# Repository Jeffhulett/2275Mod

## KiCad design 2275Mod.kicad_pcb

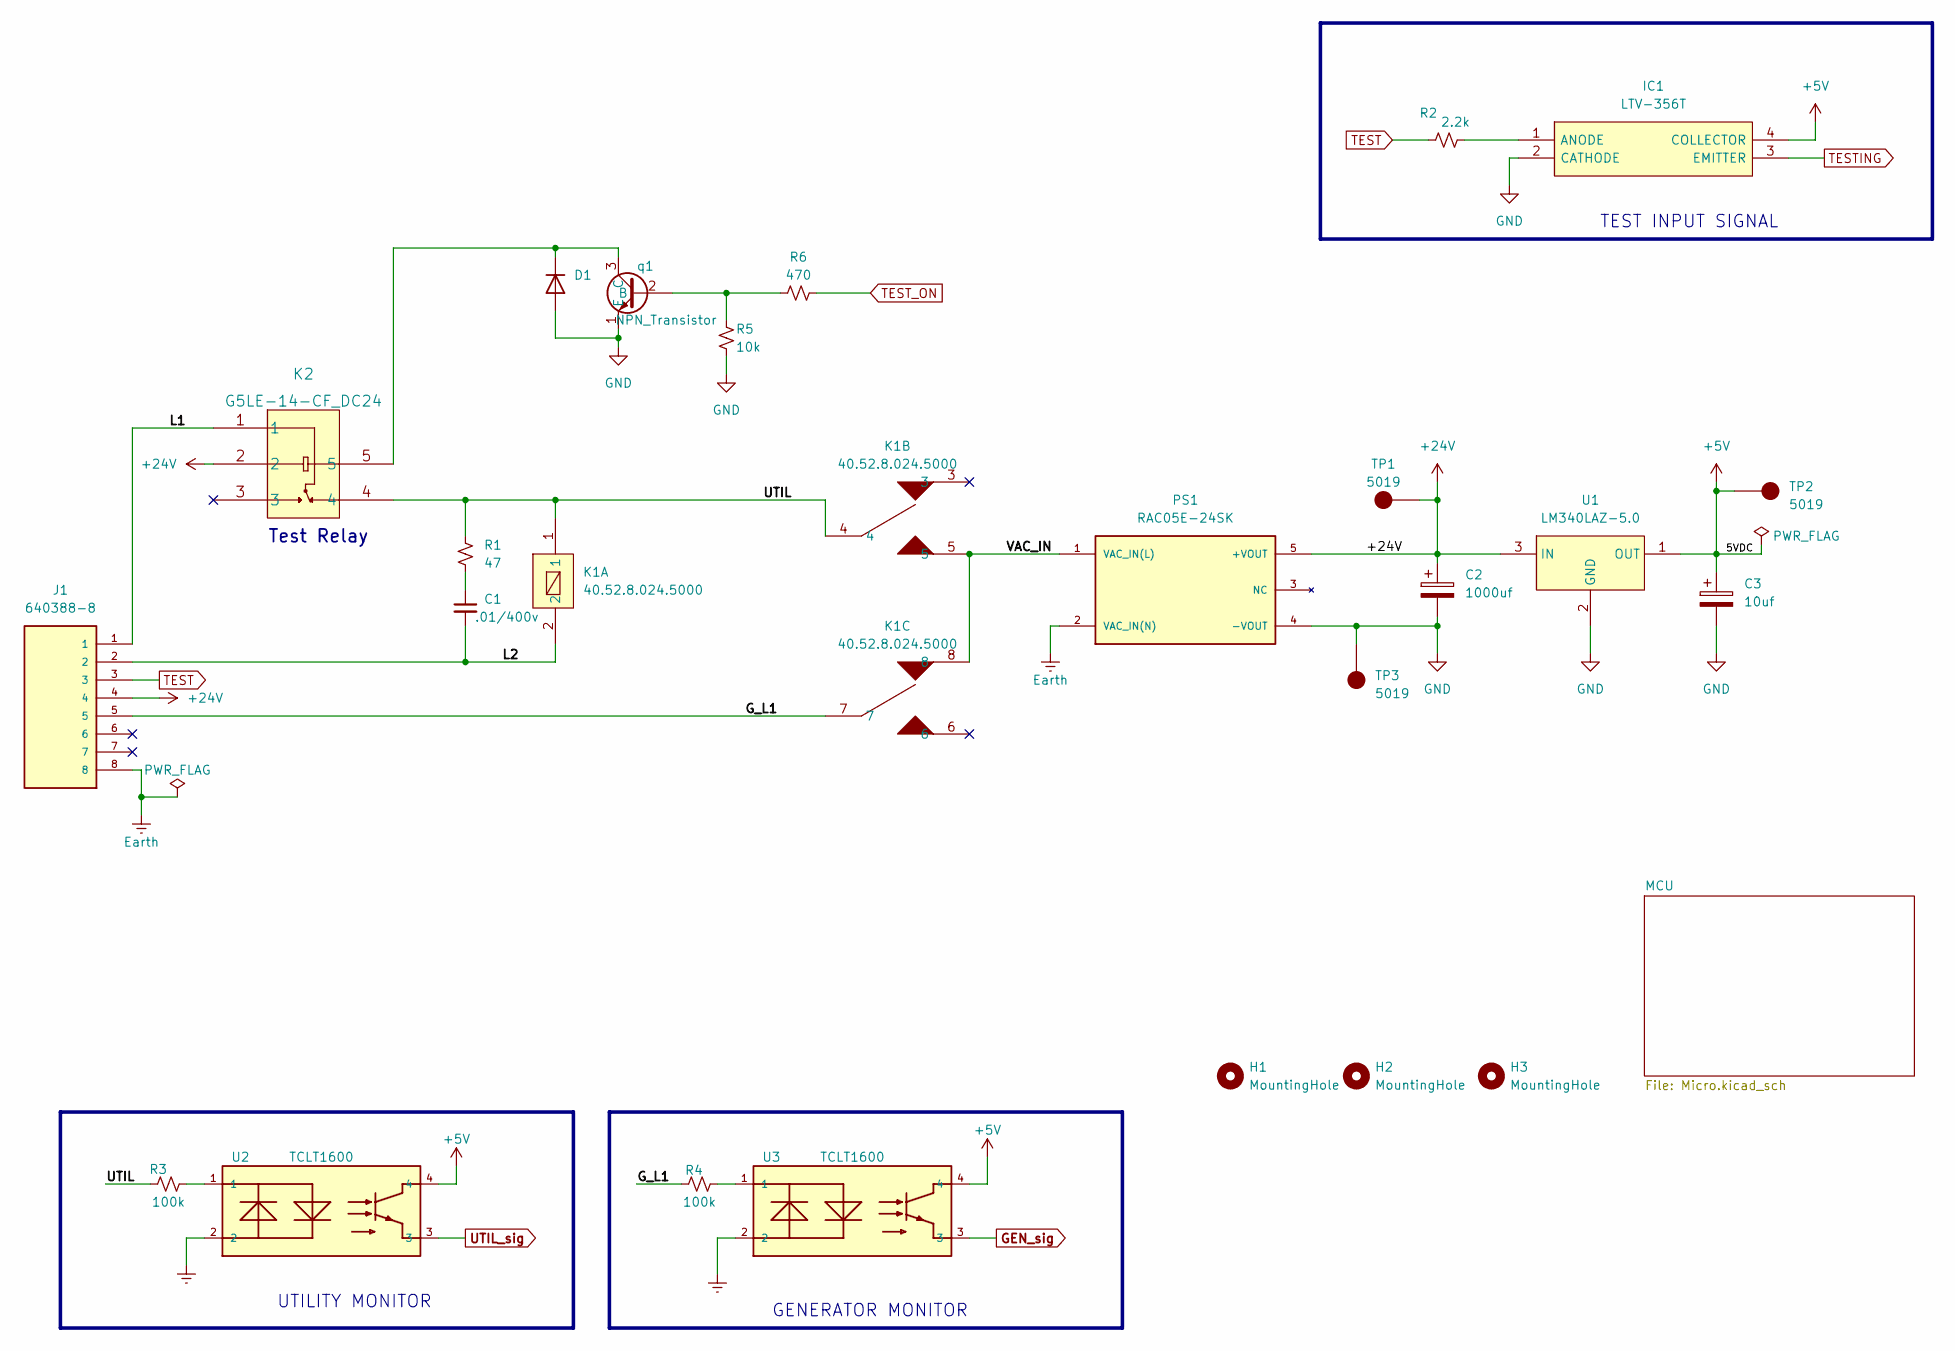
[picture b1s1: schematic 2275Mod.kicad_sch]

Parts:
C1: .01/400v; C_Rect_L9.0mm_W3.8mm_P7.50mm_MKT
C2: 1000uf; CP_Radial_D16.0mm_P7.50mm
C3: 10uf; CP_Radial_D5.0mm_P2.50mm
D1: MRA4007T3G; D_SMA
H1, H2, H3: MountingHole; MountingHole_3.7mm
IC1: LTV-356T; SOP254P675X220-4N; Mouser Part Number 859-LTV-356T
J1: 640388-8; TE_640388-8; Digi-Key part# A19906-ND
K1: 40.52.8.024.5000; 4052; Digi-Key 2066-40.52.8.024.5000-ND
K2: G5LE-14-CF_DC24; G5LE-14-CF DC24
PS1: RAC05E-24SK; CONV_RAC05E-24SK; PARTREV 0/2021
R1: 47; R_0805_2012Metric_Pad1.20x1.40mm_HandSolder
R2: 2.2k; R_0603_1608Metric_Pad0.98x0.95mm_HandSolder
R3, R4: 100k; R_1206_3216Metric_Pad1.30x1.75mm_HandSolder; Digi-Key 738-RNCP1206FTD100KCT-ND
R5: 10k; R_0603_1608Metric_Pad0.98x0.95mm_HandSolder
R6: 470; R_0603_1608Metric_Pad0.98x0.95mm_HandSolder
TP1, TP2, TP3: 5019; KEYSTONE_5019; PARTREV D
U1: LM340LAZ-5.0; TO92127P478H483-3; Digi-Key 2156-LM340LAZ-5.0-ND
U2, U3: TCLT1600; SOP254P1015X230-4N; Digi-Key TCLT1600CT-ND
q1: NPN_Transistor; SOT-23-3

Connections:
+5V: C3.1, IC1.4 (COLLECTOR), TP2.TP, U1.1 (OUT), U2.4, U3.4; also elsewhere on the board
+24V: C2.1, J1.4, K2.2, PS1.5 (+VOUT), TP1.TP, U1.3 (IN); also elsewhere on the board
/G_L1: J1.5, K1.7, R4.1
/L1: J1.1, K2.1
/L2: C1.2, J1.2, K1.2
/UTIL: K1.1, K1.4, K2.4, R1.1, R3.1
/VAC_IN: K1.5, K1.8, PS1.1 (VAC_IN(L))
Earth: J1.8, PS1.2 (VAC_IN(N)), U2.2, U3.2
GEN_sig: U3.3; also elsewhere on the board
GND: C2.2, C3.2, D1.2 (A), IC1.2 (CATHODE), PS1.4 (-VOUT), R5.2, TP3.TP, U1.2 (GND), q1.1 (E); also elsewhere on the board
unnamed: C1.1, R1.2
unnamed: D1.1 (K), K2.5, q1.3 (C)
unnamed: IC1.1 (ANODE), R2.2
unnamed: R3.2, U2.1
unnamed: R4.2, U3.1
unnamed: R5.1, R6.1, q1.2 (B)
TEST: J1.3, R2.1
TESTING: IC1.3 (EMITTER); also elsewhere on the board
TEST_ON: R6.2; also elsewhere on the board
UTIL_sig: U2.3; also elsewhere on the board

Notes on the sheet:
TEST INPUT SIGNAL
Test Relay
GENERATOR MONITOR
UTILITY MONITOR

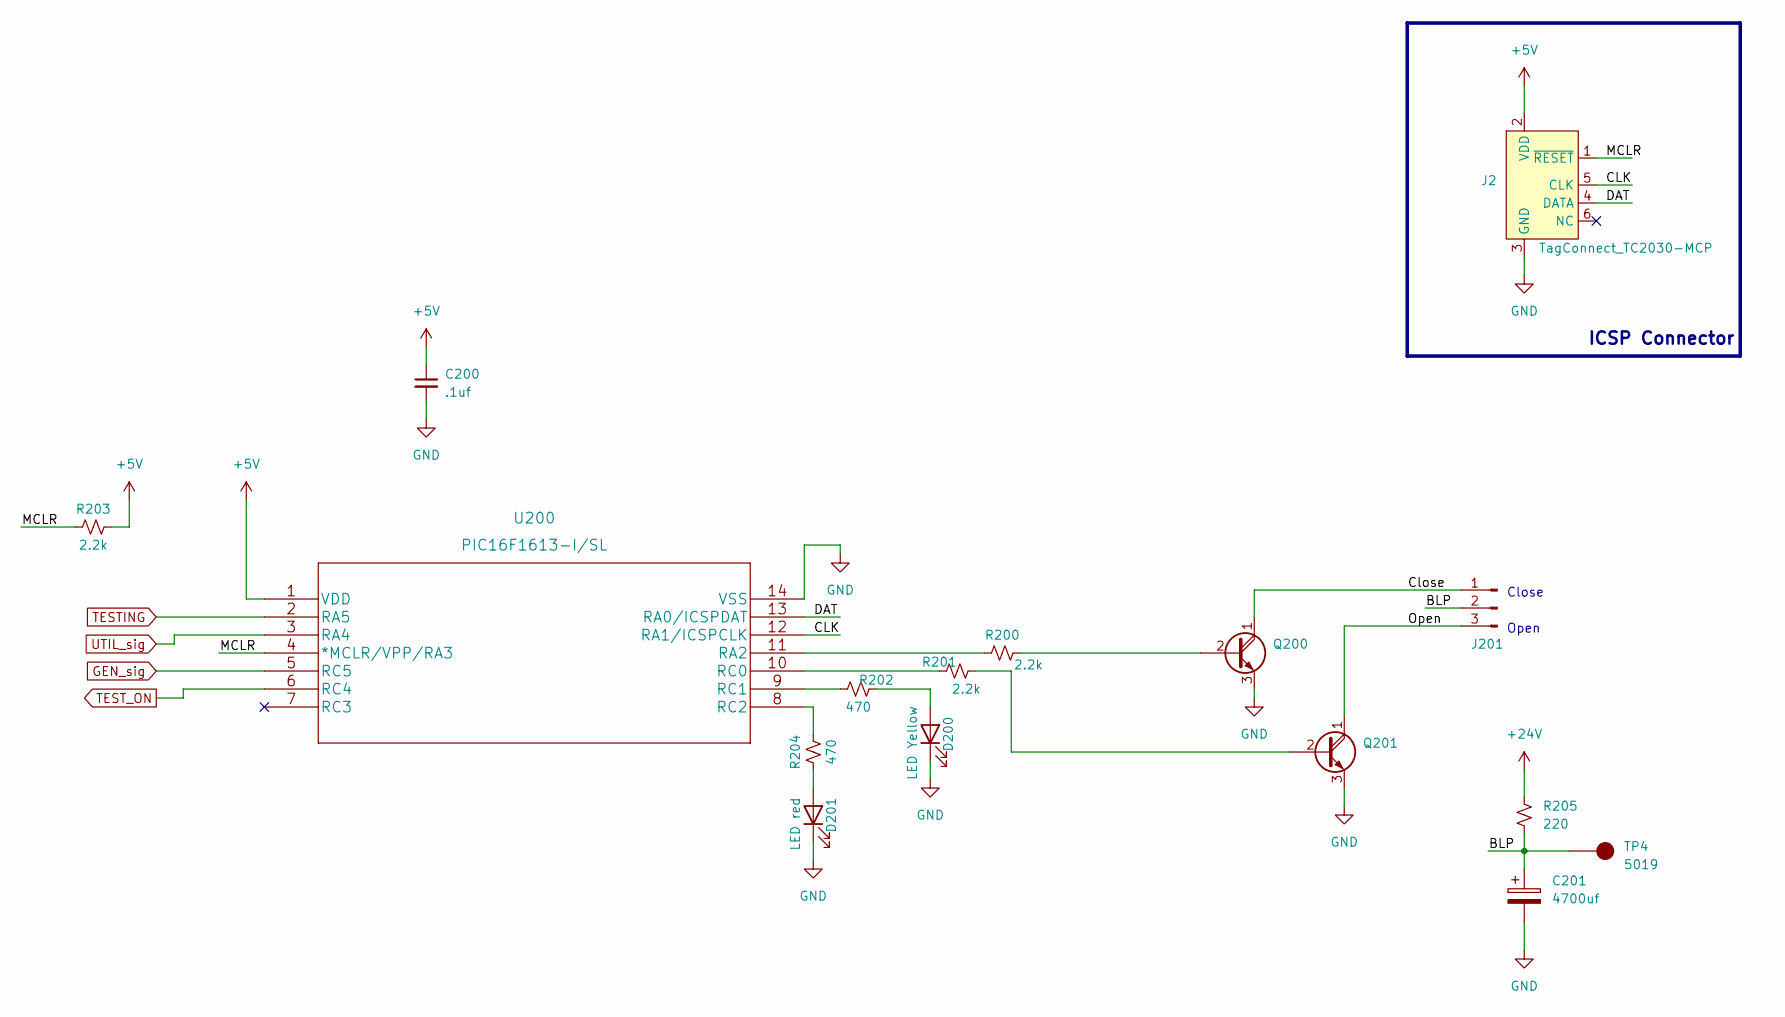
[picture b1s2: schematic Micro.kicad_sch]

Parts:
C200: .1uf; C_0603_1608Metric_Pad1.08x0.95mm_HandSolder
C201: 4700uf; CP_Radial_D25.0mm_P10.00mm_SnapIn
D200: LED Yellow; LED_0603_1608Metric_Pad1.05x0.95mm_HandSolder
D201: LED red; LED_0603_1608Metric_Pad1.05x0.95mm_HandSolder
J2: TagConnect_TC2030-MCP; Tag-Connect_TC2030-IDC-NL_2x03_P1.27mm_Vertical
J201: Conn_01x03_Male; PinHeader_1x03_P2.54mm_Vertical
Q200, Q201: Q_NPN_Darlington_CBE; SOT-223-3_TabPin2; Digi-Key FZT600BCT-ND
R200, R201, R203: 2.2k; R_0603_1608Metric_Pad0.98x0.95mm_HandSolder
R202, R204: 470; R_0805_2012Metric_Pad1.20x1.40mm_HandSolder
R205: 220; R_0805_2012Metric_Pad1.20x1.40mm_HandSolder
TP4: 5019; KEYSTONE_5019; PARTREV D
U200: PIC16F1613-I/SL; SOIC-14_3.9x8.7mm_P1.27mm; Digi-Key PIC16F1613-I/SL-ND

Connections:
+5V: C200.1, J2.2 (VDD), R203.2, U200.1 (VDD); also elsewhere on the board
+24V: R205.1; also elsewhere on the board
/MCU/BLP: C201.1, J201.2, R205.2, TP4.TP
/MCU/CLK: J2.5 (CLK), U200.12 (RA1/ICSPCLK)
/MCU/Close: J201.1, Q200.1 (C)
/MCU/DAT: J2.4 (DATA), U200.13 (RA0/ICSPDAT)
/MCU/MCLR: J2.1 (~RESET), R203.1, U200.4 (*MCLR/VPP/RA3)
/MCU/Open: J201.3, Q201.1 (C)
GEN_sig: U200.5 (RC5); also elsewhere on the board
GND: C200.2, C201.2, D200.1 (K), D201.1 (K), J2.3 (GND), Q200.3 (E), Q201.3 (E), U200.14 (VSS); also elsewhere on the board
unnamed: D200.2 (A), R202.2
unnamed: D201.2 (A), R204.1
unnamed: Q200.2 (B), R200.2
unnamed: Q201.2 (B), R201.2
unnamed: R200.1, U200.11 (RA2)
unnamed: R201.1, U200.10 (RC0)
unnamed: R202.1, U200.9 (RC1)
unnamed: R204.2, U200.8 (RC2)
TESTING: U200.2 (RA5); also elsewhere on the board
TEST_ON: U200.6 (RC4); also elsewhere on the board
UTIL_sig: U200.3 (RA4); also elsewhere on the board

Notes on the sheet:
Open
Close
ICSP Connector

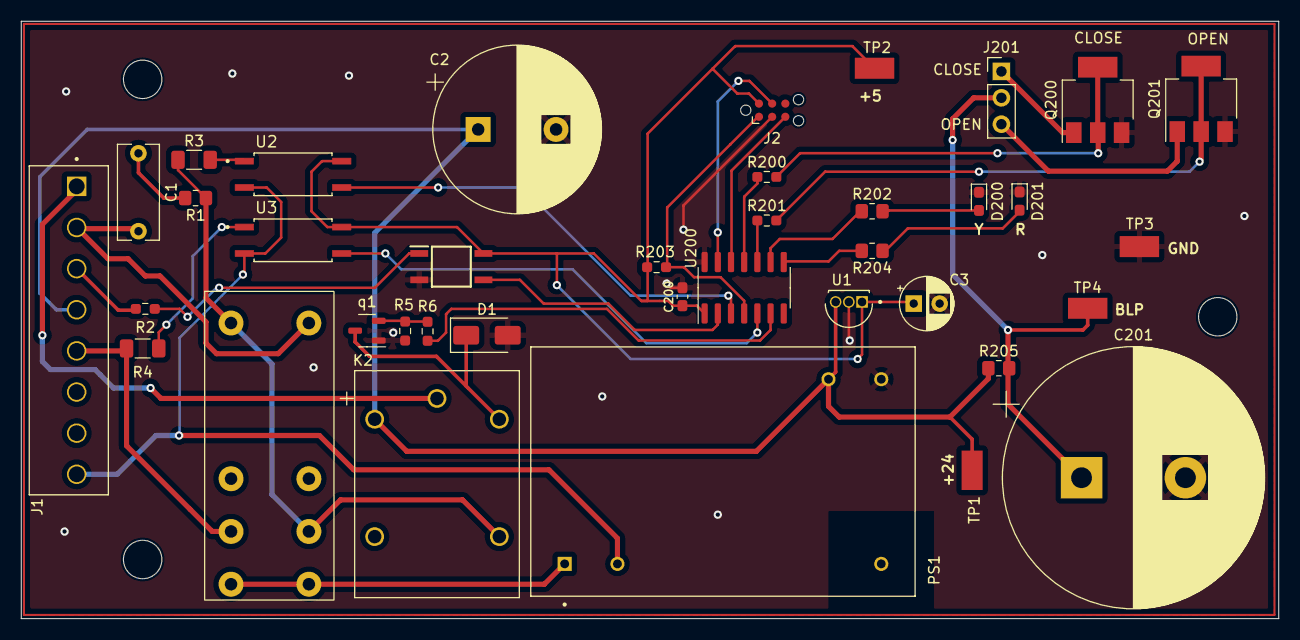
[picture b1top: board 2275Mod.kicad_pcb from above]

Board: 2 copper layers, 121.1 x 57.5 mm, 41 parts (0 on the bottom side), 34 nets.

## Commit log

2023-03-06 commit before starting kicad 7
2023-03-06 move parts on the PCB
2023-03-08 board rearrange
2023-03-15 add test points, clean up errors
2023-03-18 add test points, add open, close to connector on silk screen, add 3d model for the power supply part
2023-03-28 make some traces thicker
2023-04-01 move traces, move c200 next to micro, genral clean up
2023-04-07 corrected q200 and q201 footprints
2023-04-29 fix k1 wrong foot print re route

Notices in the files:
parts and their libraries:
Copyright 2021 Accelerated Designs. All rights reserved.
